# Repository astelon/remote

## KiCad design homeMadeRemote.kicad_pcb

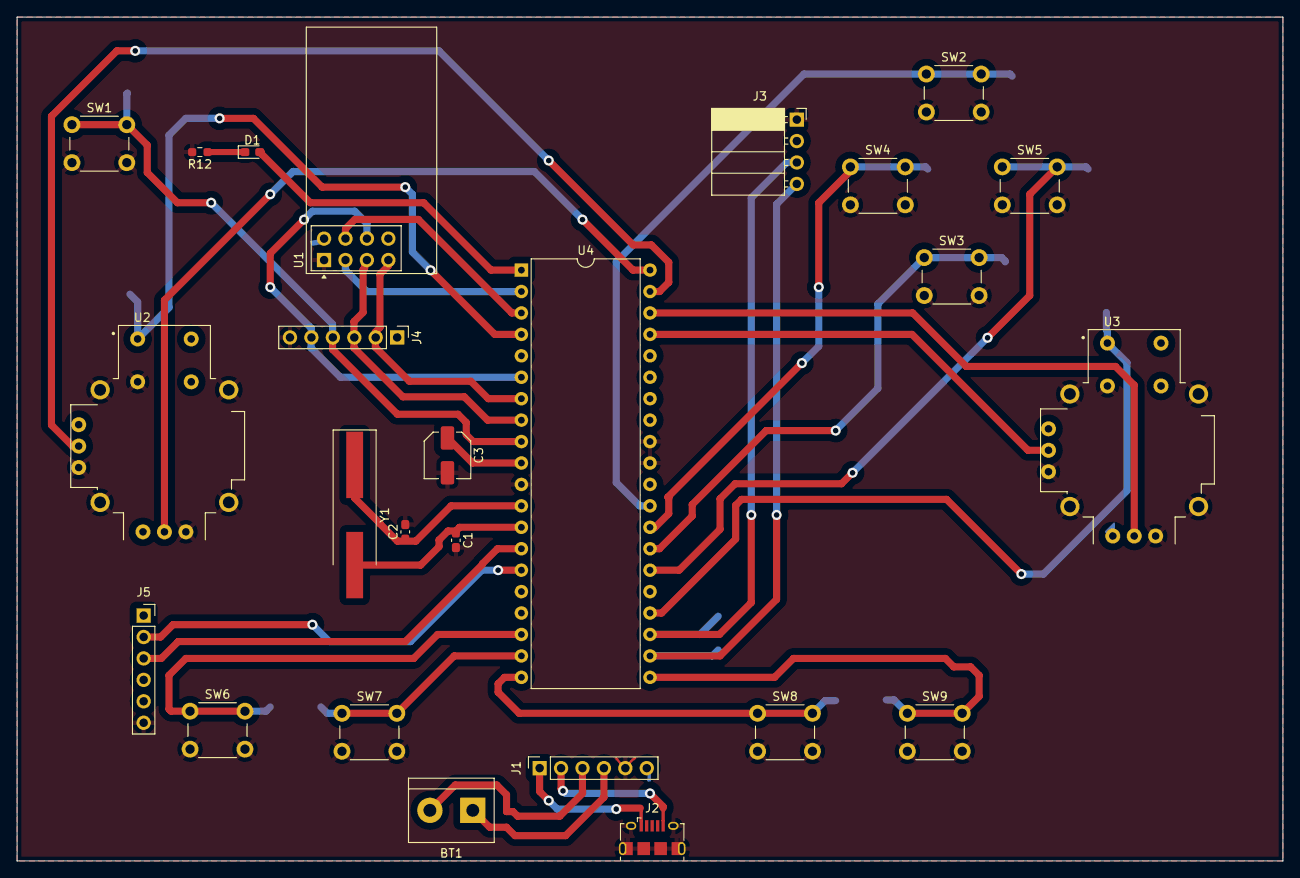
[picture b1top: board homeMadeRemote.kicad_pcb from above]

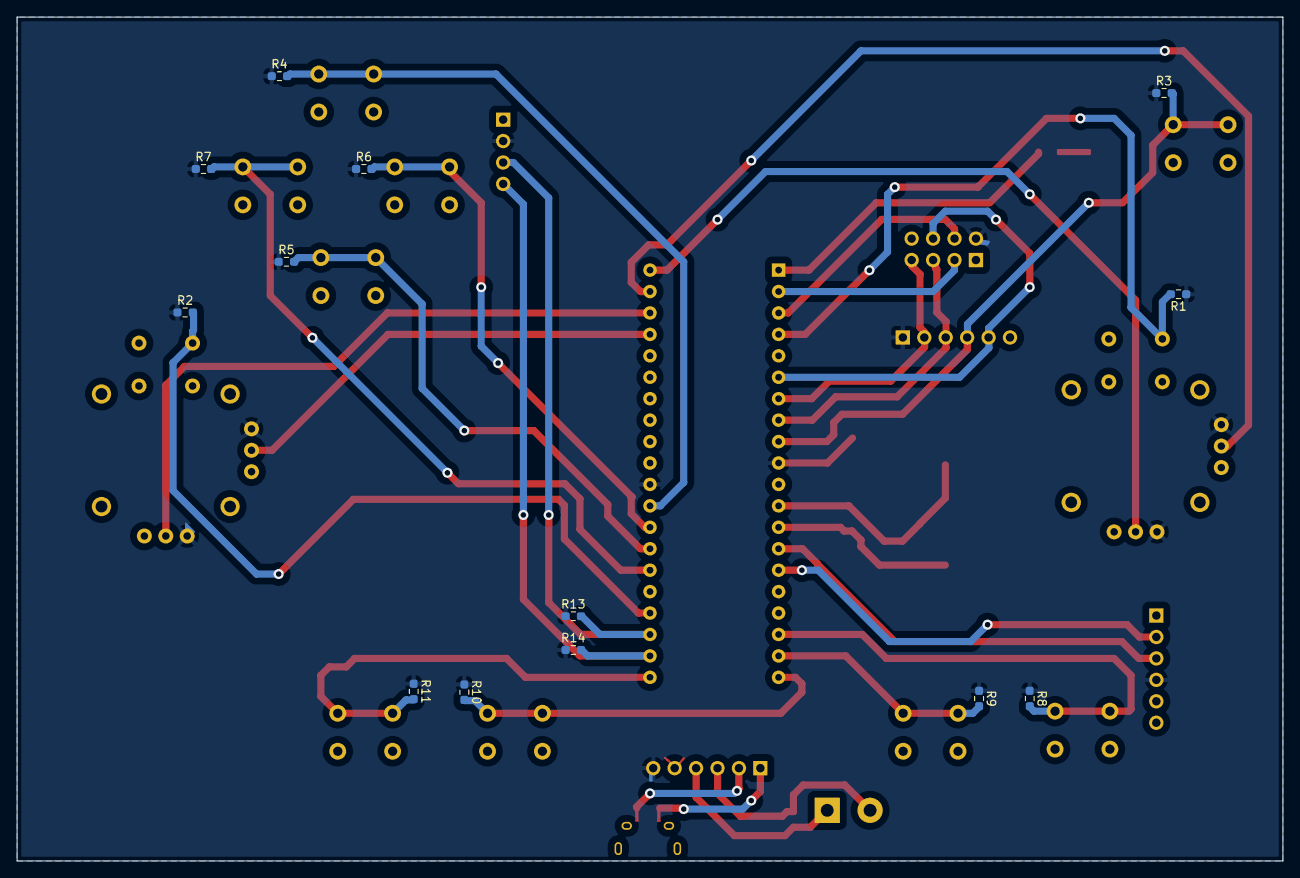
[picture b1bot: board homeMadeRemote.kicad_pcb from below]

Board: 2 copper layers, 150.0 x 100.0 mm, 38 parts (13 on the bottom side), 34 nets.

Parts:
BT1: 18650; TerminalBlock_bornier-2_P5.08mm
C1, C2: 22pF; C_0603_1608Metric_Pad1.08x0.95mm_HandSolder
C3: 10u; C_Elec_5x5.4
D1: LED; LED_0603_1608Metric_Pad1.05x0.95mm_HandSolder
J1: TP4056; PinSocket_1x06_P2.54mm_Vertical
J2: USB; USB_Micro-B_Amphenol_10118194_Horizontal
J3: LCD 2004; PinSocket_1x04_P2.54mm_Horizontal
J4: ICP; PinHeader_1x06_P2.54mm_Vertical
J5: Serial; PinSocket_1x06_P2.54mm_Vertical
R1, R2, R3, R4, R5, R6, R7, R8, R9, R10, R11, R13, R14: 10k; R_0603_1608Metric_Pad0.98x0.95mm_HandSolder
R12: 330; R_0603_1608Metric_Pad0.98x0.95mm_HandSolder
SW1, SW2, SW3, SW4, SW5, SW6, SW7, SW8, SW9: SW_Push; SW_PUSH_6mm_H4.3mm
U1: NRF24L01_Breakout; nRF24L01_Breakout
U2: Left Stick; XDCR_COM-09032
U3: Right Stick; XDCR_COM-09032
U4: ATmega644P-20P; DIP-40_W15.24mm
Y1: 16 MHz; Crystal_SMD_HC49-SD_HandSoldering

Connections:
/BTN_A: R8.2, SW6.1, U4.18 (PD4)
/BTN_B: R9.2, SW7.1, U4.19 (PD5)
/BTN_DOWN: R5.2, SW3.1, U4.27 (PC5)
/BTN_LEFT: R6.2, SW4.1, U4.28 (PC6)
/BTN_RIGHT: R7.2, SW5.1, U4.26 (PC4)
/BTN_UP: R4.2, SW2.1, U4.29 (PC7)
/BTN_X: R10.2, SW8.1, U4.20 (PD6)
/BTN_Y: R11.2, SW9.1, U4.21 (PD7)
/BatteryGnd: BT1.2 (-), J1.3
/BatteryVcc: BT1.1 (+), J1.4
/JL_Click: R1.2, U2.B1A (SEL+), U4.4 (PB3)
/JL_X: U2.H2 (H), U4.40 (PA0)
/JL_Y: U2.V2 (V), U4.39 (PA1)
/JR_Click: R2.2, U3.B1A (SEL+), U4.24 (PC2)
/JR_X: U3.H2 (H), U4.38 (PA2)
/JR_Y: U3.V2 (V), U4.37 (PA3)
/LED: D1.2 (A), U4.1 (PB0)
/MISO: J4.2, U1.7 (MISO), U4.7 (PB6)
/MOSI: J4.5, U1.6 (MOSI), U4.6 (PB5)
/RESET_N: J4.4, R3.2, SW1.1, U4.9 (~RESET)
/RXD0: J5.3, U4.14 (PD0)
/SCK: J4.3, U1.5 (SCK), U4.8 (PB7)
/SCL: J3.4, R14.2, U4.22 (PC0)
/SDA: J3.3, R13.2, U4.23 (PC1)
/TXD0: J5.2, U4.15 (PD1)
/UsbGnd: J1.2, J2.5 (GND)
/UsbVin: J1.1, J2.1 (VBUS)
/W_CE: U1.3 (CE), U4.2 (PB1)
/W_CSN: U1.4 (~CSN), U4.3 (PB2)
GND: C1.2, C2.2, C3.2, J1.5, J2.6 (Shield), J3.1, J4.6, J5.6, R12.2, SW1.2, SW2.2, SW3.2, SW4.2, SW5.2, SW6.2, SW7.2, SW8.2, SW9.2, U1.1 (GND), U2.B2A (SEL-), U2.H3 (H-), U2.S1 (SHIELD), U2.S2 (SHIELD), U2.S3 (SHIELD), U2.S4 (SHIELD), U2.V3 (V-), U3.B2A (SEL-), U3.H3 (H-), U3.S1 (SHIELD), U3.S2 (SHIELD), U3.S3 (SHIELD), U3.S4 (SHIELD), U3.V3 (V-), U4.11 (GND), U4.31 (GND), U4.32 (AREF)
unnamed: D1.1 (K), R12.1
unnamed: C1.1, U4.13 (XTAL1), Y1.2
unnamed: C2.1, U4.12 (XTAL2), Y1.1
VCC: C3.1, J1.6, J3.2, J4.1, J5.4, R1.1, R2.1, R3.1, R4.1, R5.1, R6.1, R7.1, R8.1, R9.1, R10.1, R11.1, R13.1, R14.1, U1.2 (VCC), U2.H1 (H+), U2.V1 (V+), U3.H1 (H+), U3.V1 (V+), U4.10 (VCC), U4.30 (AVCC)
